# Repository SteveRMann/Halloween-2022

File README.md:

# MonsterBox
This project is further development of the 2021 monster in a box for Halloween.
The biggest change is the addition of a bubble generator.

## Crate Ideas
Contains images and ideas for the crate construction

## Fan
Contains the schematic files for the fan and LED MOSFET controller.

## Notes
Just contains random notes used while making the box

## Sounds
Contains the sound files and editing information. It also contains the DFPlayer notes.

## src
### dfPlayer
This is the code that controls the sounds from the box

### HBridgeTest
Code to test the H-Bridge. This year we changed to a library to control the tail H-bridge

### Lid
Contains the Arduino source code for the lid mechanism.

### servoSweep
Code to sweep the servo 0-180 degrees.

### servoManualSweep
Code used to calibrate the PWM endpoints for servo.h

### tail
Code to make the sea monster's tail sweep back and forth.

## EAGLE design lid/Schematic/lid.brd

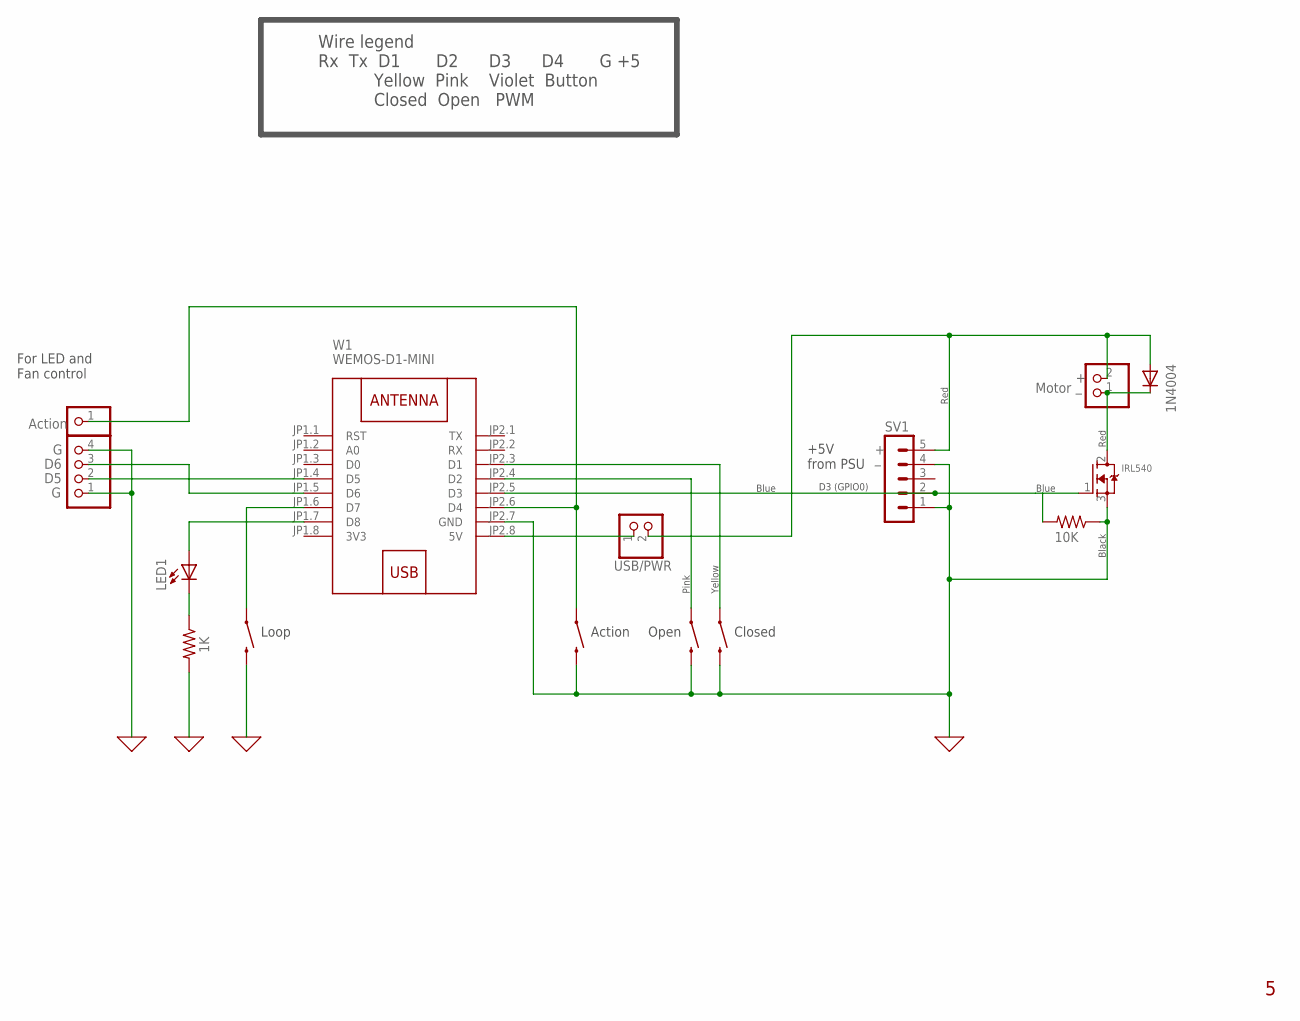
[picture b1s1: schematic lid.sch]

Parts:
ACTION, ACTION1: MOMENTARY-SWITCH-SPST-PTH-6.0MM; TACTILE_SWITCH_PTH_6.0MM
D1: 1N4004; DO41-10
JP1: PINHD-1X1; 1X01
JP3: PINHD-1X2; 1X02
JP4: PINHD-1X4; 1X04
LED1: LED5MM
Q1: IRL540; TO220V
R1: 1K; 0207/10
R4: 10K; 0207/10
S1, S2: MOMENTARY-SWITCH-SPST-PTH-6.0MM; TACTILE_SWITCH_PTH_6.0MM
SV1: MA05-1
USB/PWR: PINHD-1X2; 1X02
W1: WEMOS-D1-MINI

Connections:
0: ACTION.3 (2), ACTION1.3 (2), JP4.1, JP4.4, Q1.3 (S), R1.2, R4.1, S1.3 (2), S2.3 (2), SV1.1, SV1.4, W1.JP2.7 (GND)
3V3: W1.JP1.8 (3V3)
unnamed: Q1.1 (G), R4.2, SV1.2, W1.JP2.5 (D3)
unnamed: D1.C, JP3.1, Q1.2 (D)
unnamed: D1.A, JP3.2, SV1.5, USB/PWR.2
unnamed: S1.1, W1.JP2.4 (D2)
unnamed: S2.1, W1.JP2.3 (D1)
unnamed: LED1.A, W1.JP1.7 (D8)
unnamed: LED1.K (C), R1.1
unnamed: USB/PWR.1, W1.JP2.8 (5V)
unnamed: ACTION.1, JP1.1, W1.JP2.6 (D4)
unnamed: JP4.2, W1.JP1.4 (D5)
unnamed: JP4.3, W1.JP1.5 (D6)
unnamed: ACTION1.1, W1.JP1.6 (D7)

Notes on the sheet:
Motor
+5V from PSU
D3 (GPIO0)
Open
Closed
Yellow
Pink
Blue
Black
Red
Action
Wire legend Rx Tx D1 D2 D3 D4 G +5 Yellow Pink Violet Button Closed Open PWM
For LED and Fan control
Loop

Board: 2 copper layers, 15 parts (0 on the bottom side), 13 nets, no tracks yet.

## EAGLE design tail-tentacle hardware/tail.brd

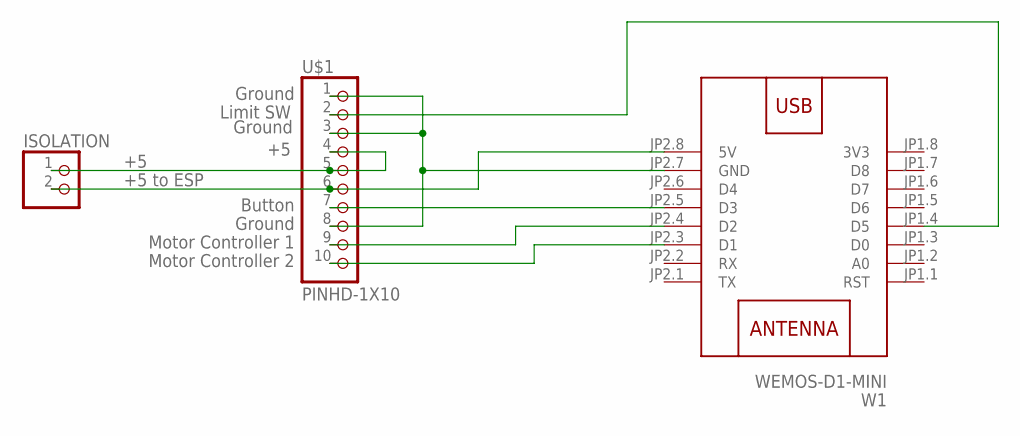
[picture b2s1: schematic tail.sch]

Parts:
ISOLATION: PINHD-1X2; 1X02
U$1: PINHD-1X10; 1X10-BIG
W1: WEMOS-D1-MINI

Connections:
3V3: W1.JP1.8 (3V3)
unnamed: U$1.7, W1.JP2.5 (D3)
unnamed: U$1.9, W1.JP2.4 (D2)
unnamed: U$1.10, W1.JP2.3 (D1)
unnamed: ISOLATION.1, U$1.4, U$1.5
unnamed: ISOLATION.2, U$1.6, W1.JP2.8 (5V)
unnamed: U$1.2, W1.JP1.4 (D5)
unnamed: U$1.1, U$1.3, U$1.8, W1.JP2.7 (GND)

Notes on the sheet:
Limit SW
Ground
Button
Motor Controller 1
Motor Controller 2
+5 to ESP

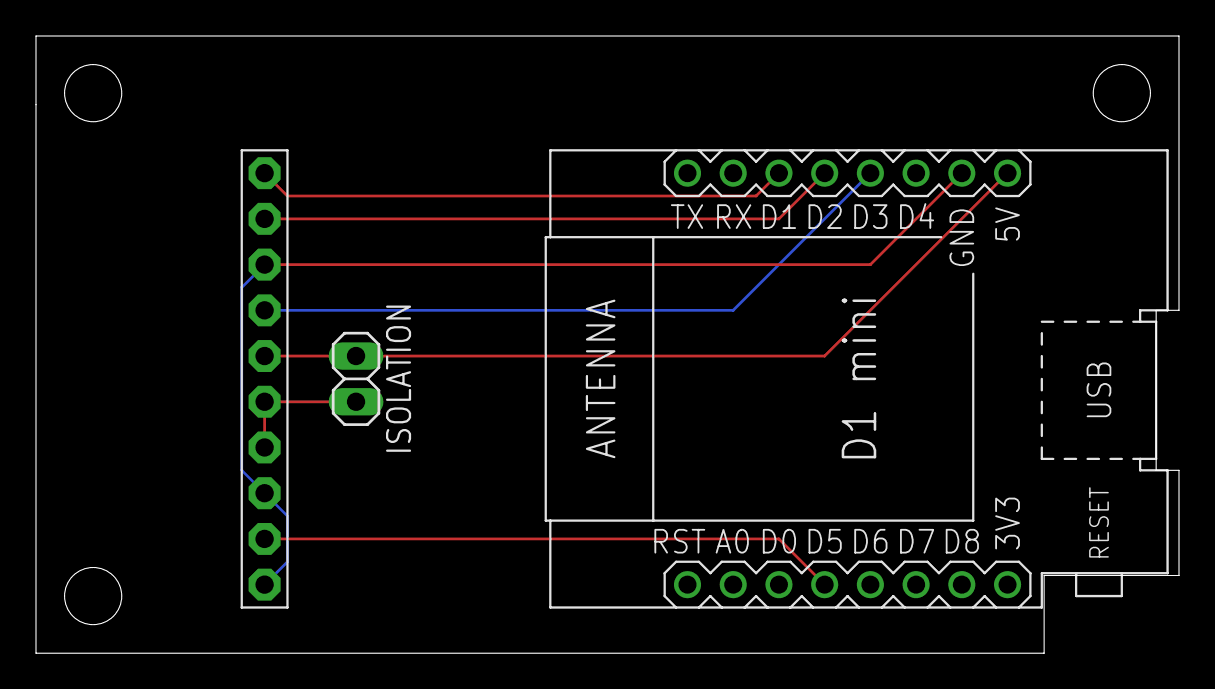
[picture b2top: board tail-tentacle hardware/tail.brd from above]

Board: 2 copper layers, 63.5 x 34.3 mm, 3 parts (0 on the bottom side), 7 nets.

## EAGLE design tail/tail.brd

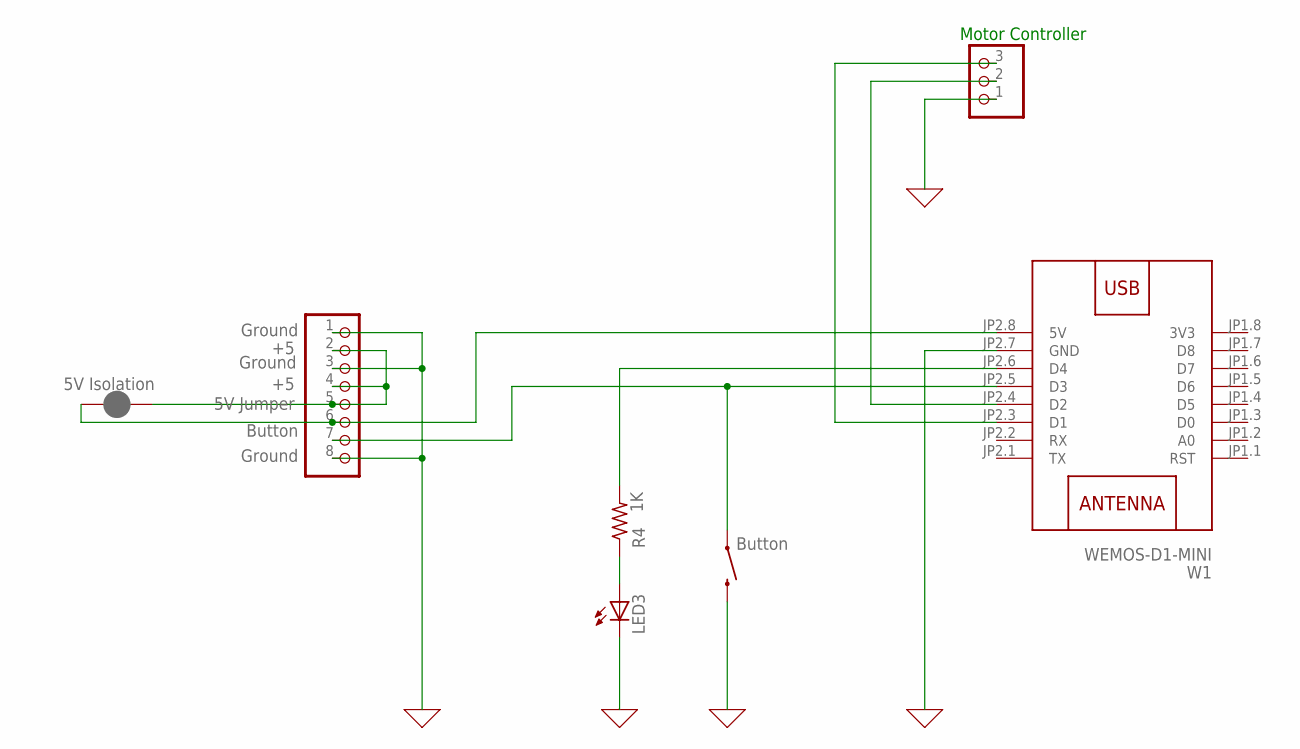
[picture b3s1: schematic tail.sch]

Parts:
JP1: PINHD-1X8BIG; 1X08-BIG
JP2: PINHD-1X3; 1X03
JP3: JUMPER-SMT_2_NC_PASTE_NO-SILK; SMT-JUMPER_2_NC_PASTE_NO-SILK
LED3: LED5MM
R4: 1K; 0207/10
S1: MOMENTARY-SWITCH-SPST-PTH-6.0MM; TACTILE_SWITCH_PTH_6.0MM
W1: WEMOS-D1-MINI

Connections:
0: JP1.1, JP1.3, JP1.8, JP2.1, LED3.K (C), S1.3 (2), W1.JP2.7 (GND)
3V3: W1.JP1.8 (3V3)
unnamed: JP2.2, W1.JP2.4 (D2)
unnamed: JP2.3, W1.JP2.3 (D1)
unnamed: JP1.2, JP1.4, JP1.5, JP3.2
unnamed: JP1.6, JP3.1, W1.JP2.8 (5V)
unnamed: R4.2, W1.JP2.6 (D4)
unnamed: LED3.A, R4.1
unnamed: JP1.7, S1.1, W1.JP2.5 (D3)

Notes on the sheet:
Button
Ground
Motor Controller
5V Jumper
5V Isolation

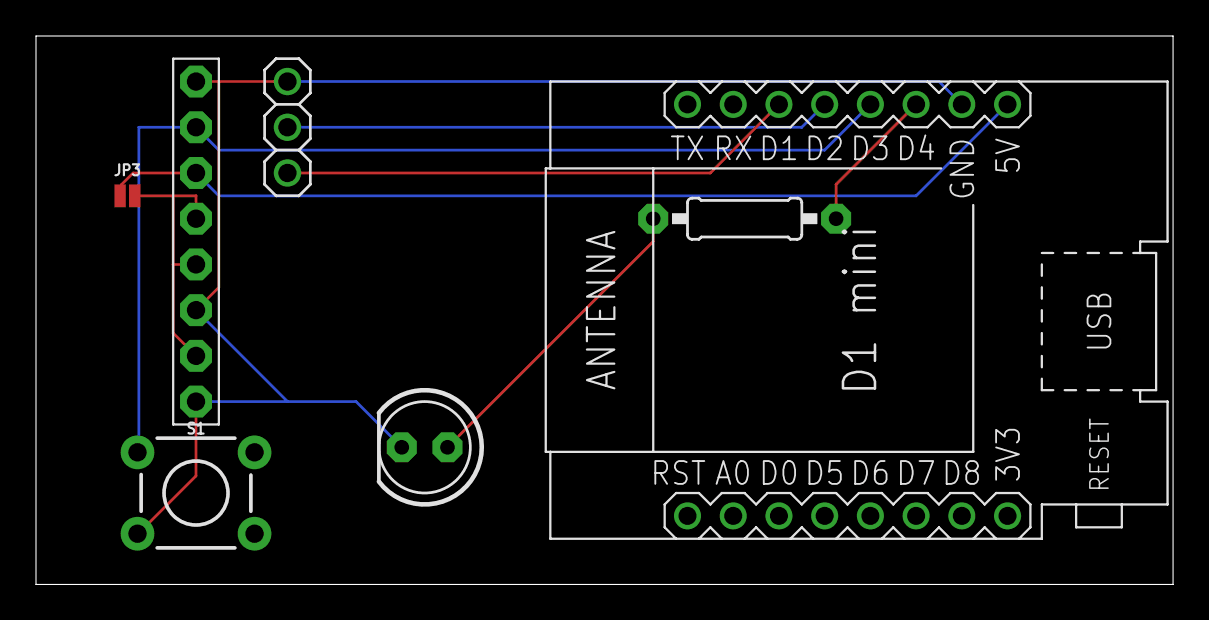
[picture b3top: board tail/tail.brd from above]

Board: 2 copper layers, 63.2 x 30.5 mm, 7 parts (0 on the bottom side), 8 nets.

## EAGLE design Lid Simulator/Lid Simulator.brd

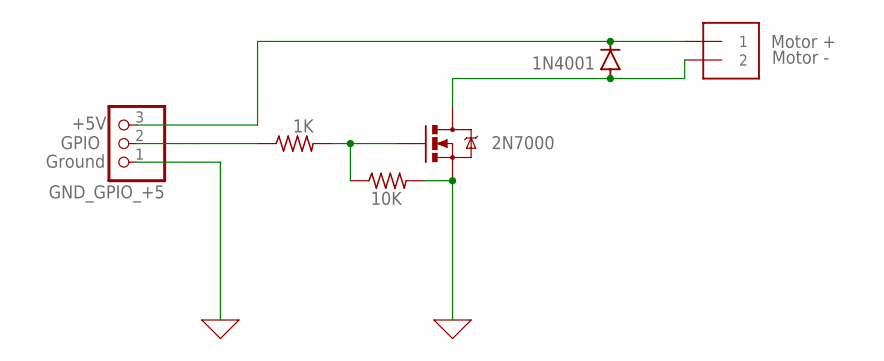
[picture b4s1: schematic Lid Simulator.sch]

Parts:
D1: 1N4001; DO-41
GND_GPIO_+5: PINHD-1X3CB; 1X03-CLEANBIG
MOTOR_-__+: 1X2-3.5MM
Q1: MOSFET-NCHANNEL2N7000; TO-92
R1: 1K; 0207/10
R2: 10K; 0207/10

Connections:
0: GND_GPIO_+5.1, Q1.1 (S), R2.2
unnamed: D1.A, MOTOR_-__+.2, Q1.3 (D)
unnamed: Q1.2 (G), R1.2, R2.1
unnamed: GND_GPIO_+5.2, R1.1
unnamed: D1.C, GND_GPIO_+5.3, MOTOR_-__+.1

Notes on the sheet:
Motor +
Motor -
+5V
GPIO
Ground
2N7000

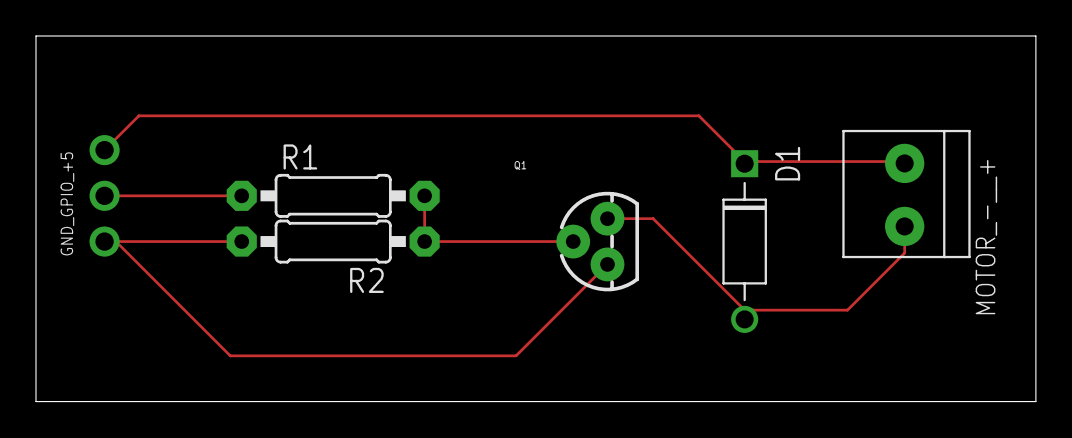
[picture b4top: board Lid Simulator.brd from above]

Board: 2 copper layers, 55.5 x 20.3 mm, 6 parts (0 on the bottom side), 5 nets.

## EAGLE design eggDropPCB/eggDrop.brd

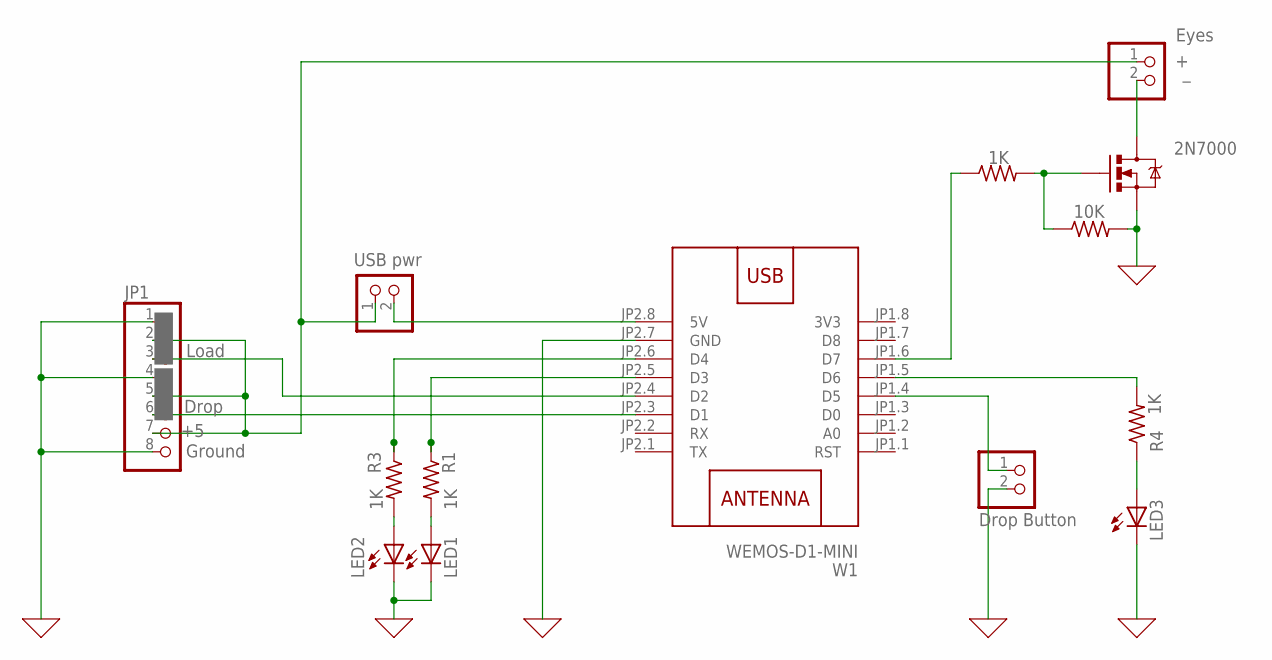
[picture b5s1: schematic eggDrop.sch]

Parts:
2N7000: MOSFET-NCHANNEL2N7000; TO-92
JP1: PINHD-1X8BIG; 1X08-BIG
JP2: USB pwr; 1X02
JP3: Drop Button; 1X02
JP4: Eyes; 1X02
LED1, LED2, LED3: LED5MM
R1, R3, R4, R5: 1K; 0207/10
R2: 10K; 0207/10
W1: WEMOS-D1-MINI

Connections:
0: 2N7000.1 (S), JP1.1, JP1.4, JP1.8, JP3.2, LED1.K (C), LED2.K (C), LED3.K (C), R2.2, W1.JP2.7 (GND)
3V3: W1.JP1.8 (3V3)
unnamed: JP1.2, JP1.5, JP1.7, JP2.1, JP4.1
unnamed: JP2.2, W1.JP2.8 (5V)
unnamed: 2N7000.3 (D), JP4.2
unnamed: JP1.6, W1.JP2.3 (D1)
unnamed: R3.1, W1.JP2.6 (D4)
unnamed: LED1.A, R1.2
unnamed: LED2.A, R3.2
unnamed: R4.2, W1.JP1.5 (D6)
unnamed: LED3.A, R4.1
unnamed: JP3.1, W1.JP1.4 (D5)
unnamed: JP1.3, W1.JP2.4 (D2)
unnamed: R1.1, W1.JP2.5 (D3)
unnamed: 2N7000.2 (G), R2.1, R5.2
unnamed: R5.1, W1.JP1.6 (D7)

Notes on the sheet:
Drop
Load
Ground

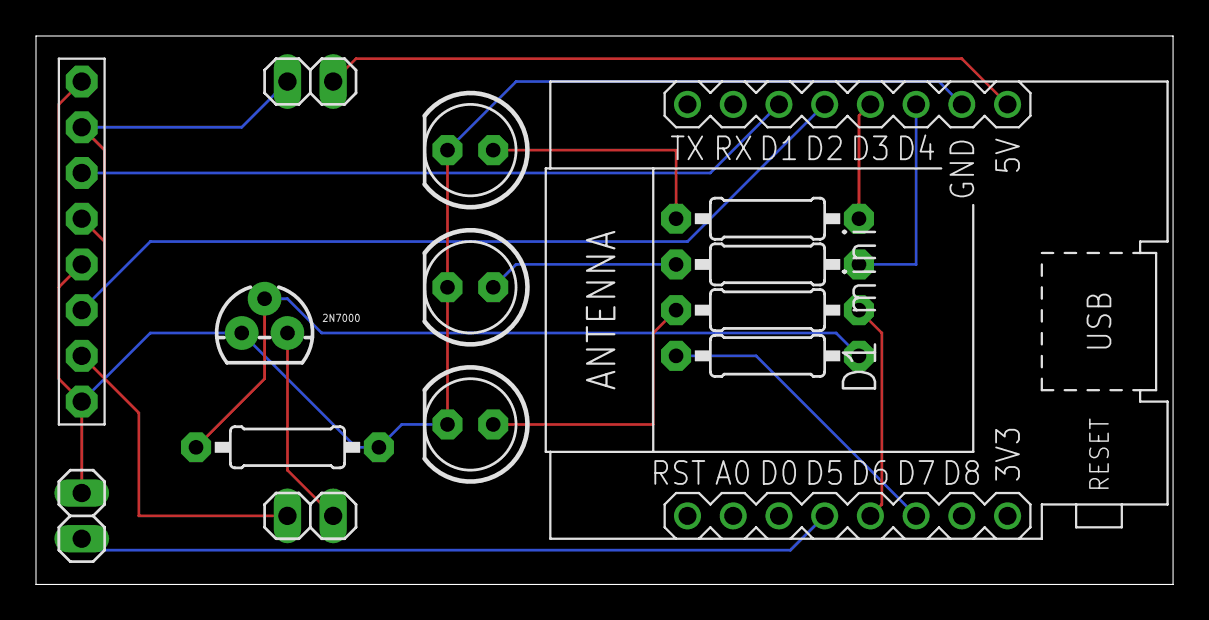
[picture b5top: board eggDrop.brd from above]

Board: 2 copper layers, 63.2 x 30.5 mm, 14 parts (0 on the bottom side), 15 nets.

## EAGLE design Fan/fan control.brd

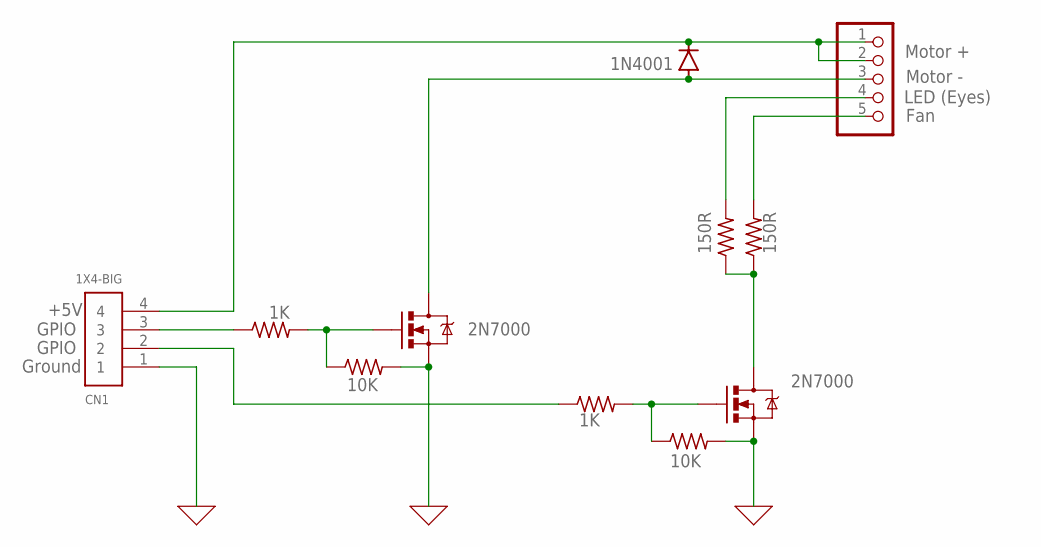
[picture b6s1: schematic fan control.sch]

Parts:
CN1: 1X4-BIG; 1X04-BIG
D1: 1N4001; DO-41
JP1: PINHD-1X5; 1X05
Q1, Q2: MOSFET-NCHANNEL2N7000; TO-92
R1, R3: 1K; 0207/10
R2, R4: 10K; 0207/10
R5, R6: 150R; 0207/10

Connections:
0: CN1.1, Q1.1 (S), Q2.1 (S), R2.2, R4.2
unnamed: CN1.4, D1.C, JP1.1, JP1.2
unnamed: Q1.2 (G), R1.2, R2.1
unnamed: CN1.3, R1.1
unnamed: D1.A, JP1.3, Q1.3 (D)
unnamed: Q2.2 (G), R3.2, R4.1
unnamed: Q2.3 (D), R5.1, R6.1
unnamed: CN1.2, R3.1
unnamed: JP1.5, R6.2
unnamed: JP1.4, R5.2

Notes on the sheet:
Motor +
Motor -
+5V
GPIO
Ground
2N7000
LED (Eyes)
Fan

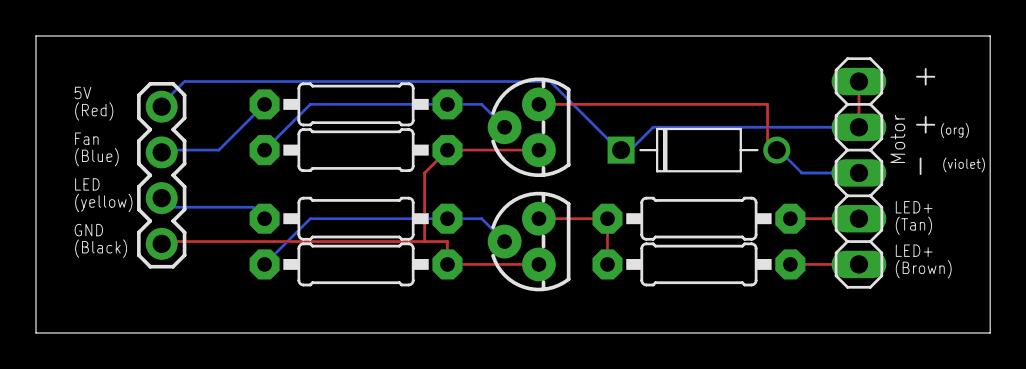
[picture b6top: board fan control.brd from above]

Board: 2 copper layers, 53.0 x 16.5 mm, 11 parts (0 on the bottom side), 10 nets.

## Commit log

2021-09-21 Add files via upload
    eggDropTest is the terminal version of the program. Used for testing servo operation and timing.
2021-09-22 Added mqtt and OTA
2021-09-24 Added WiFi, OTA and MQTT
2021-09-25 Added OneButton.h library for single, double and long button presses
2021-09-27 Added lid schematic
2021-09-28 Changed GPIO pin numbers.
2021-09-28 Added LED/FAN GPIO ports
2021-09-28 Added LED and FAN GPIO ports
2021-09-28 Changed schematic filename
2021-10-02 Rename .gitignore to .gitignore_global
2021-10-06 Added 'blink' to eggDrop
2021-10-06 Added button multifunction to eggDrop
2021-10-09 Refresh the git
2021-10-09 Added syncTopic
2021-10-09 Testing the Git
2021-10-09 Removed cleanup.bat
2021-10-10 Worked on sync
2021-10-10 Added Pumpkin Videos directory to gitignore.
2021-10-10 Shorter growl sound
2021-10-11 timings for the sync feature
2021-10-11 Changed the delay after 'roar'
    The track2 length changed.
2021-10-11 Changed the exit servo zero position.
2021-10-11 Changed eyes to analog, added sync()
    Changed eyes to analog to adjust the brightness. Added blink.
    Added sync()
2021-10-12 Added NoDelay-Function-Experiments.ino
2021-10-12 Blink and Dim are using nodelay.h
2021-10-12 Changed 'eyes' to 'peek'
2021-10-12 Update functions.ino
    Reduce the delay for letting the motor move past the limit switches. This, of course, assumes that the motor actually stoppen ON a liit switch.
2021-10-12 Update Lid.ino
    Commented out the peek functions
2021-10-12 Update loop.ino
    Removed the peek() function with delays
2021-10-12 Update mqttcallback.ino
    removed the sync lines with delays.
2021-10-12 Update setup.ino
    Temp- commented out the timers starts.
2021-10-13 Update functions.ino
    startTheMotor(), changed the delay after startup to just testing the switches. Also slowed the run speed.
2021-10-14 Update functions.ino
    Removed some superfluous print statements
2021-10-14 Update Lid.ino
    Removed peek functions
2021-10-14 Update loop.ino
    Removed peek stuff
2021-10-14 Update mqttcallback.ino
    Changed digitalWrite(EYES_PIN) to analogWrite
2021-10-14 Update setup.ino
    Removed peeks
2021-10-15 Update functions.ino
    Remove syncCheck
2021-10-15 Update Lid.ino
    Added syncOpen and syncClose
2021-10-15 Update loop.ino
    Added sync_open_timer and sync_close_timer
2021-10-15 Update mqttcallback.ino
    Started to remove syncTopic
2021-10-15 Update setup.ino
    Setup syncTbl
2021-10-15 Update Version number
2021-10-15 Update mqttcallback.ino
    Added MQTT cmnd message "roar"
2021-10-15 Update functions.ino
    Added MQTT dfplayer/cmnd message "roar"
2021-10-15 Update Lid.ino
    Update the Version numbers
2021-10-15 Update mqttcallback.ino
    Publish a msg to DFplayer/cmnd, "roar".
2021-10-15 Update Lid.ino
    Added version description
2021-10-15 Added peek
2021-10-17 Added client.publish ("tail/cmnd", "wag"); where lid opens.
2021-10-18 Added random wag
    Added noDelay() to do a slow wag at random times.
2021-10-22 Fiddled with the wags
2021-10-22 Added pumpkin video veg file
2021-10-28 Update mqtt commands.txt
    Added some comments describing the operation over MQTT commands.
2021-10-31 Removed syncTopic, added some debug print lines
2021-11-02 Added simulation mode
2021-11-03 Added h-bridge notes and links
2022-09-05 Renamed crate folder to crate ideas
2022-09-05 Update notes and lid schematic
    Update notes and lid schematic
2022-09-18 Update project files
2022-09-18 Added Audacity project files
2022-09-18 Updating orginazation
2022-09-18 Update files
2022-09-18 update changed gitignore
2022-09-18 Update MQTT.ino with dynamic hostname
2022-09-19 Moved video folders to videos folder
2022-09-19 Clean up
2022-09-19 Moved from Drive D:
2022-09-23 Added simulator
2022-09-23 Removed sync functions
2022-09-25 Changed WiFi to WiFiMulti
2022-09-25 Added motortest
2022-09-28 Working on masking the logo
2022-10-02 Changed from wifi.ino to multiWifi.h
2022-10-05 Many changes
    Added HBridgeTest.ino, cleaned up functions.ino, added namespaces, removed mqtt.ino; added myMqtt.h, added myFunctions.h, myMqtt.h,, WifiMulti.h, removed ota.ino; added myOTA.h, cleaned up setup.ino 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
2022-10-05 Allowed jpg uploads
2022-10-05 Allowed jpg to upload
2022-10-07 minor changes
2022-10-12 Mostly changing the motor timers to a state machine.
2022-10-15 Corrected spelling
    On the PC, #include is not case sensitive. It is on Linux.
2022-10-17 Made tentacle.ino from tail then tailtest.
2022-10-18 Changed tail to tentacle
2022-10-18 Cloned lid.ino to lid2.ino
    Removed OTA, MQTT, etc.
2022-10-19 Made dfplayer2 from dfplayer, without mqtt or console menu.
2022-10-21 Deleted unused code segments
2022-10-27 Removed duplicate video files
2022-10-27 Added code for rats and testing servo
2024-02-12 Video sources updated

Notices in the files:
parts and their libraries:
diy-modules: Released under the Creative Commons Attribution 4.0 International License: http://creativecommons.org/licenses/by/4.0
SparkFun-Switches: Licensing: Creative Commons ShareAlike 4.0 International - https://creativecommons.org/licenses/by-sa/4.0
